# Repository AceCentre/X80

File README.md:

# X80

X80 is an Arduino-based multi-functional input/output device designed to be an interface between assistive technology inputs such as accessibility switches or specilist sensors and mainstream technology outputs, such as to a mobile phone or Augmentative and Alternative Communication (AAC) device.

An X80 can be preprogrammed and repurposed to perform a different function. It's built around the Adafruit Feather, generally the nrf82540 Express. It's essentially a Feather Wing for Assistive Technology (AT).

There are a couple of smilar projects:

https://github.com/google/mimosa

https://github.com/asterics/FABI

The PCB is still a work in progress but it is designed to have:

* Switch inputs via 3.5mm jack
* switch outputs via 3.5mm jack (simulates a switch press as an input into an Assistive Technology device)
* DB9 connector designed to accomodate devices meeting the TRACE SET Standard often used with accessibility input devices (https://park.org/Guests/Trace/pavilion/setdoc1.htm)
* buzzer
* potentiometer
* on/off switch

There are a few differences between the prototype versions:

## Version 4

The funtionality has been split into two boards:

* X80 Standard (designed for Adafruit ItsyBitsy nrf52840 https://www.adafruit.com/product/4481)
* X80 Power (required for LIPO battery as this board includes the chargin circuit)

### X80 Standard

* Majority surface mount components
* 4 switch inputs (5 with splitter cable on one port)
* 4 switch outputs
* One switch 'pass through' (one switch input will still control on switch output without power)
* buzzer
* setting potentiometer
* header for connecting X80 Power or wiring direct to board)

### X80 Power

* JST connector for LIPO battery
* DB9 connector for connecting external peripherals
* will allow space in enclosure for LIPO battery

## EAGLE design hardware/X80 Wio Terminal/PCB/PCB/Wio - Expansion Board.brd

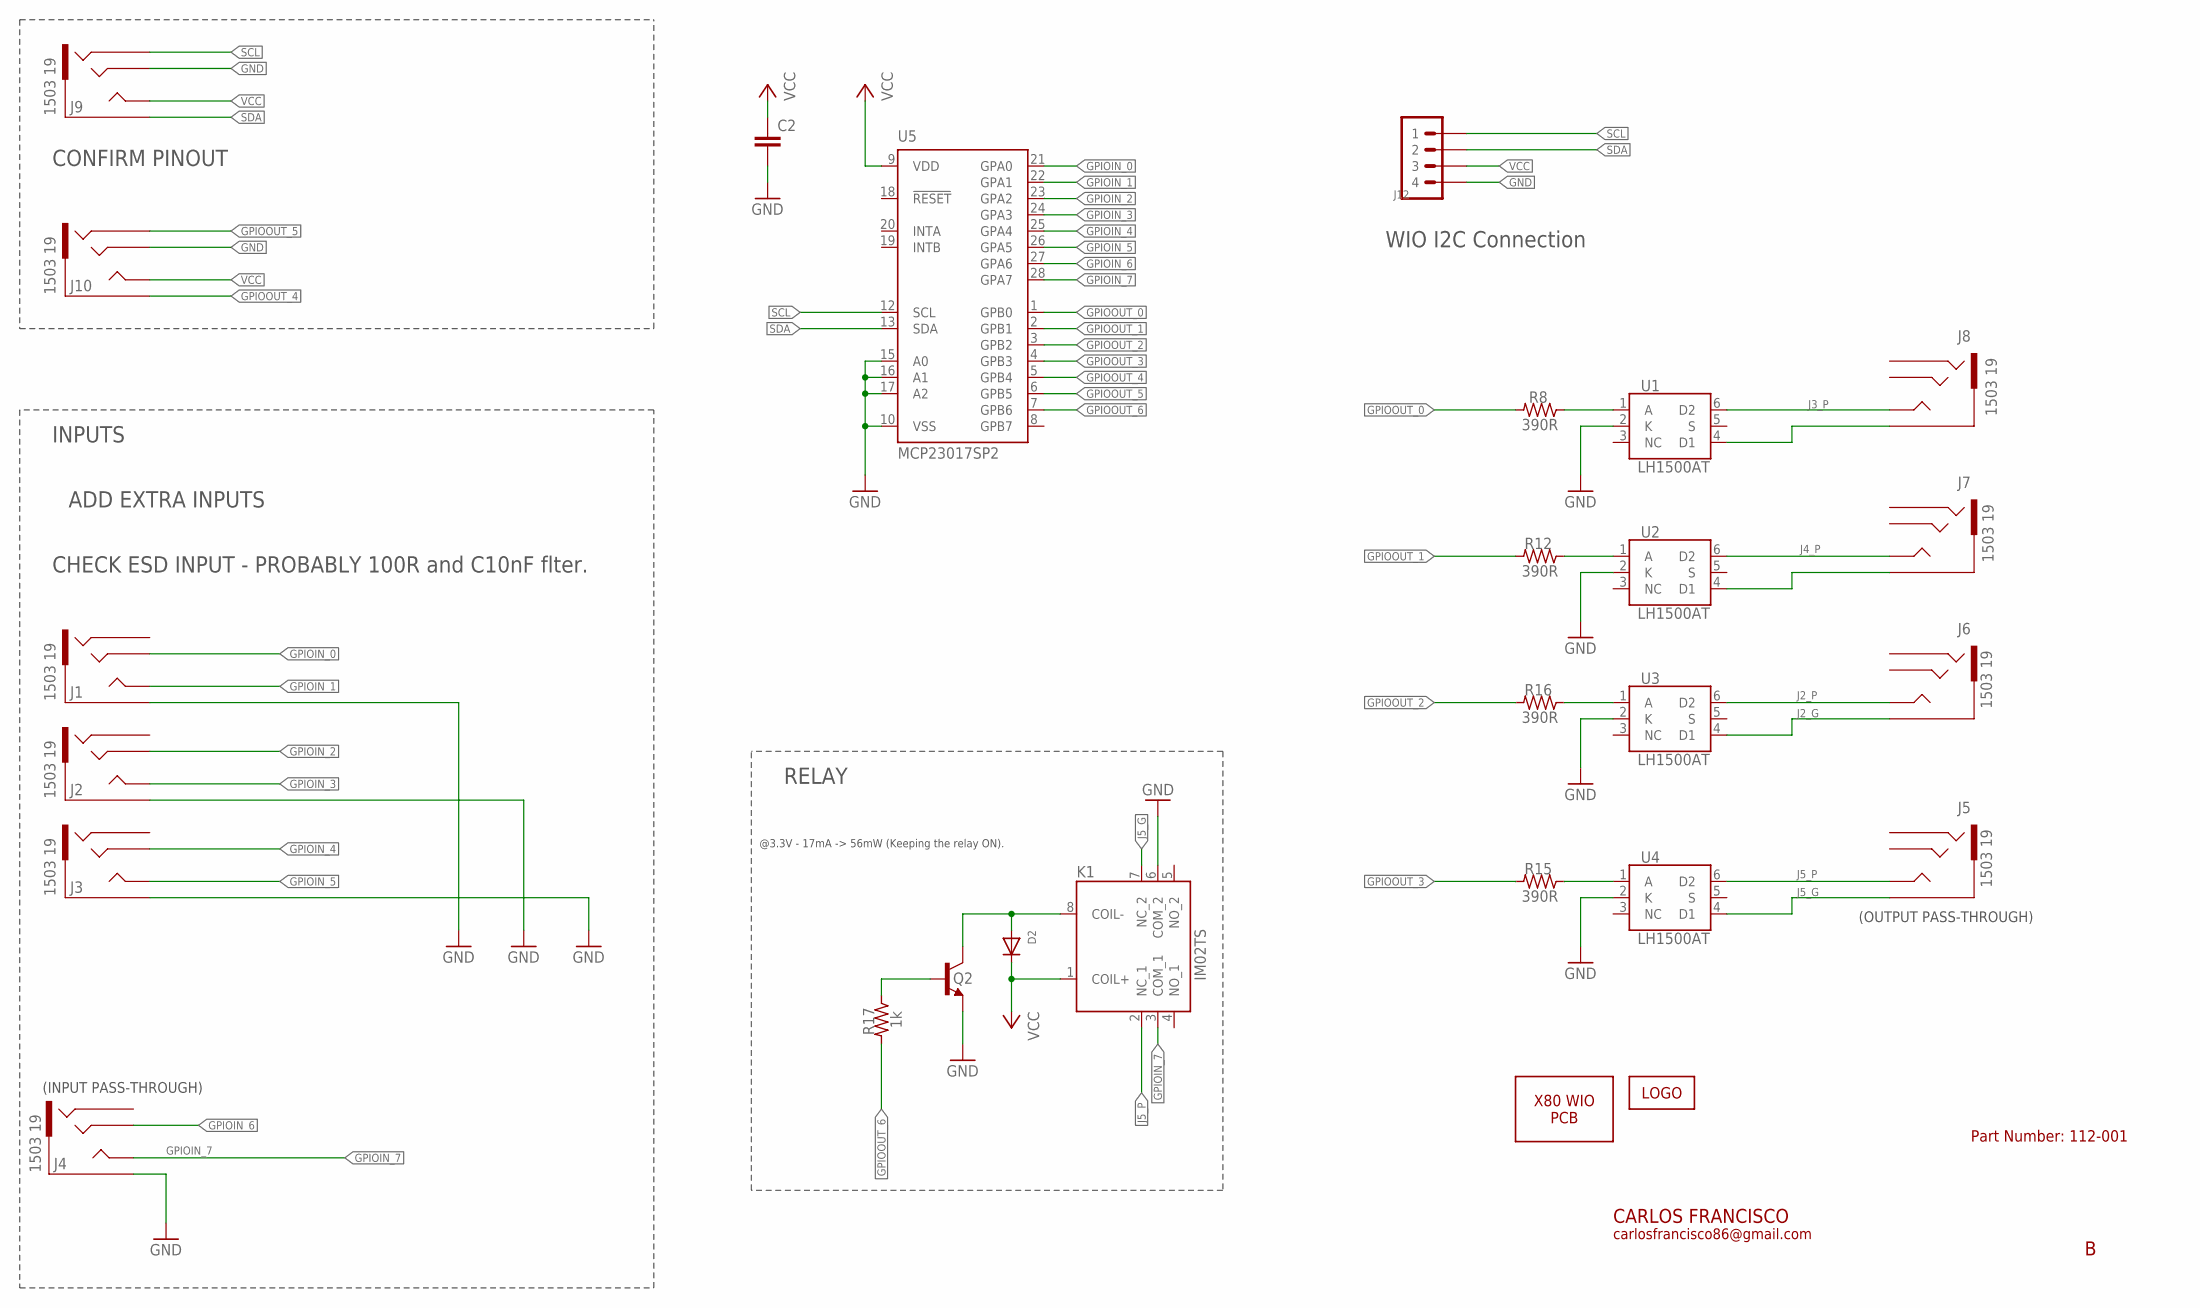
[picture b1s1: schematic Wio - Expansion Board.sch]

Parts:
C2: C-EU025-025X050; C025-025X050
D2: 1N4148; DO-1N4148
J1, J2, J3, J4, J5, J6, J7, J8, J9, J10: 1503 19; 1503-19
J12: 4P-2.0-90D; HW4-2.0-90D
K1: IM02TS; IM03TS114620378
LOGO1: LOGO-10MM; LOGO_10MM
PCB2: X80_WIO_PCB-WIO_PCB_V1; WIO_PCB
Q2: PN2222A; TO92-EBC-OVAL
R8, R12, R15, R16: 390R; 0204/7
R17: 1k; 0204/7
U1, U2, U3, U4: LH1500AT; DIP762W47P254L880H410Q6N
U5: MCP23017SP2; DIL28-3-ROUND

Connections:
GND: C2.2, J1.1, J2.1, J3.1, J4.1, J9.3, J10.3, J12.4, K1.6 (COM_2), Q2.E, U1.2 (K), U2.2 (K), U3.2 (K), U4.2 (K), U5.10 (VSS), U5.15 (A0), U5.16 (A1), U5.17 (A2)
GPIOIN_0: J1.3, U5.21 (GPA0)
GPIOIN_1: J1.4, J1.5 (4), U5.22 (GPA1)
GPIOIN_2: J2.3, U5.23 (GPA2)
GPIOIN_3: J2.4, J2.5 (4), U5.24 (GPA3)
GPIOIN_4: J3.3, U5.25 (GPA4)
GPIOIN_5: J3.4, J3.5 (4), U5.26 (GPA5)
GPIOIN_6: J4.3, U5.27 (GPA6)
GPIOIN_7: J4.4, J4.5 (4), K1.3 (COM_1), U5.28 (GPA7)
GPIOOUT_0: R8.1, U5.1 (GPB0)
GPIOOUT_1: R12.1, U5.2 (GPB1)
GPIOOUT_2: R16.1, U5.3 (GPB2)
GPIOOUT_3: R15.1, U5.4 (GPB3)
GPIOOUT_4: J10.1, U5.5 (GPB4)
GPIOOUT_5: J10.2, U5.6 (GPB5)
GPIOOUT_6: R17.1, U5.7 (GPB6)
J2_G: J6.1, U3.4 (D1)
J2_P: J6.4, J6.5 (4), U3.6 (D2)
J3_P: J8.4, J8.5 (4), U1.6 (D2)
J4_P: J7.4, J7.5 (4), U2.6 (D2)
J5_G: J5.1, K1.7 (NC_2), U4.4 (D1)
J5_P: J5.4, J5.5 (4), K1.2 (NC_1), U4.6 (D2)
unnamed: J8.1, U1.4 (D1)
unnamed: J7.1, U2.4 (D1)
unnamed: R8.2, U1.1 (A)
unnamed: R12.2, U2.1 (A)
unnamed: R16.2, U3.1 (A)
unnamed: R15.2, U4.1 (A)
unnamed: D2.A, K1.8 (COIL-), Q2.C
unnamed: Q2.B, R17.2
SCL: J9.2, J12.1, U5.12 (SCL)
SDA: J9.1, J12.2, U5.13 (SDA)
VCC: C2.1, D2.C, J9.4, J9.5 (4), J10.4, J10.5 (4), J12.3, K1.1 (COIL+), U5.9 (VDD)

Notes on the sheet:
CARLOS FRANCISCO
carlosfrancisco86@gmail.com
(INPUT PASS-THROUGH)
INPUTS
(OUTPUT PASS-THROUGH)
RELAY
Part Number: 112-001
@3.3V - 17mA -> 56mW (Keeping the relay ON).
CONFIRM PINOUT
ADD EXTRA INPUTS
WIO I2C Connection
CHECK ESD INPUT - PROBABLY 100R and C10nF flter.

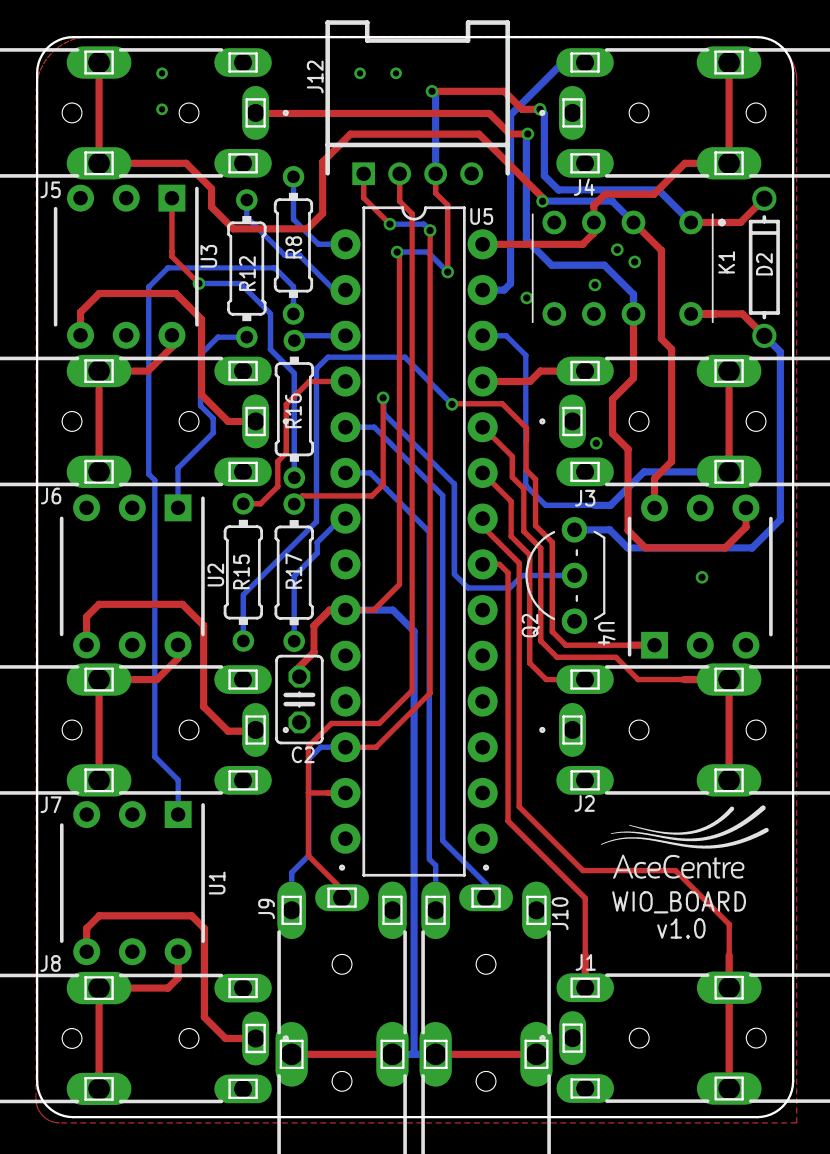
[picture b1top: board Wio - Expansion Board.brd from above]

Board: 2 copper layers, 42.0 x 60.0 mm, 27 parts (0 on the bottom side), 33 nets.

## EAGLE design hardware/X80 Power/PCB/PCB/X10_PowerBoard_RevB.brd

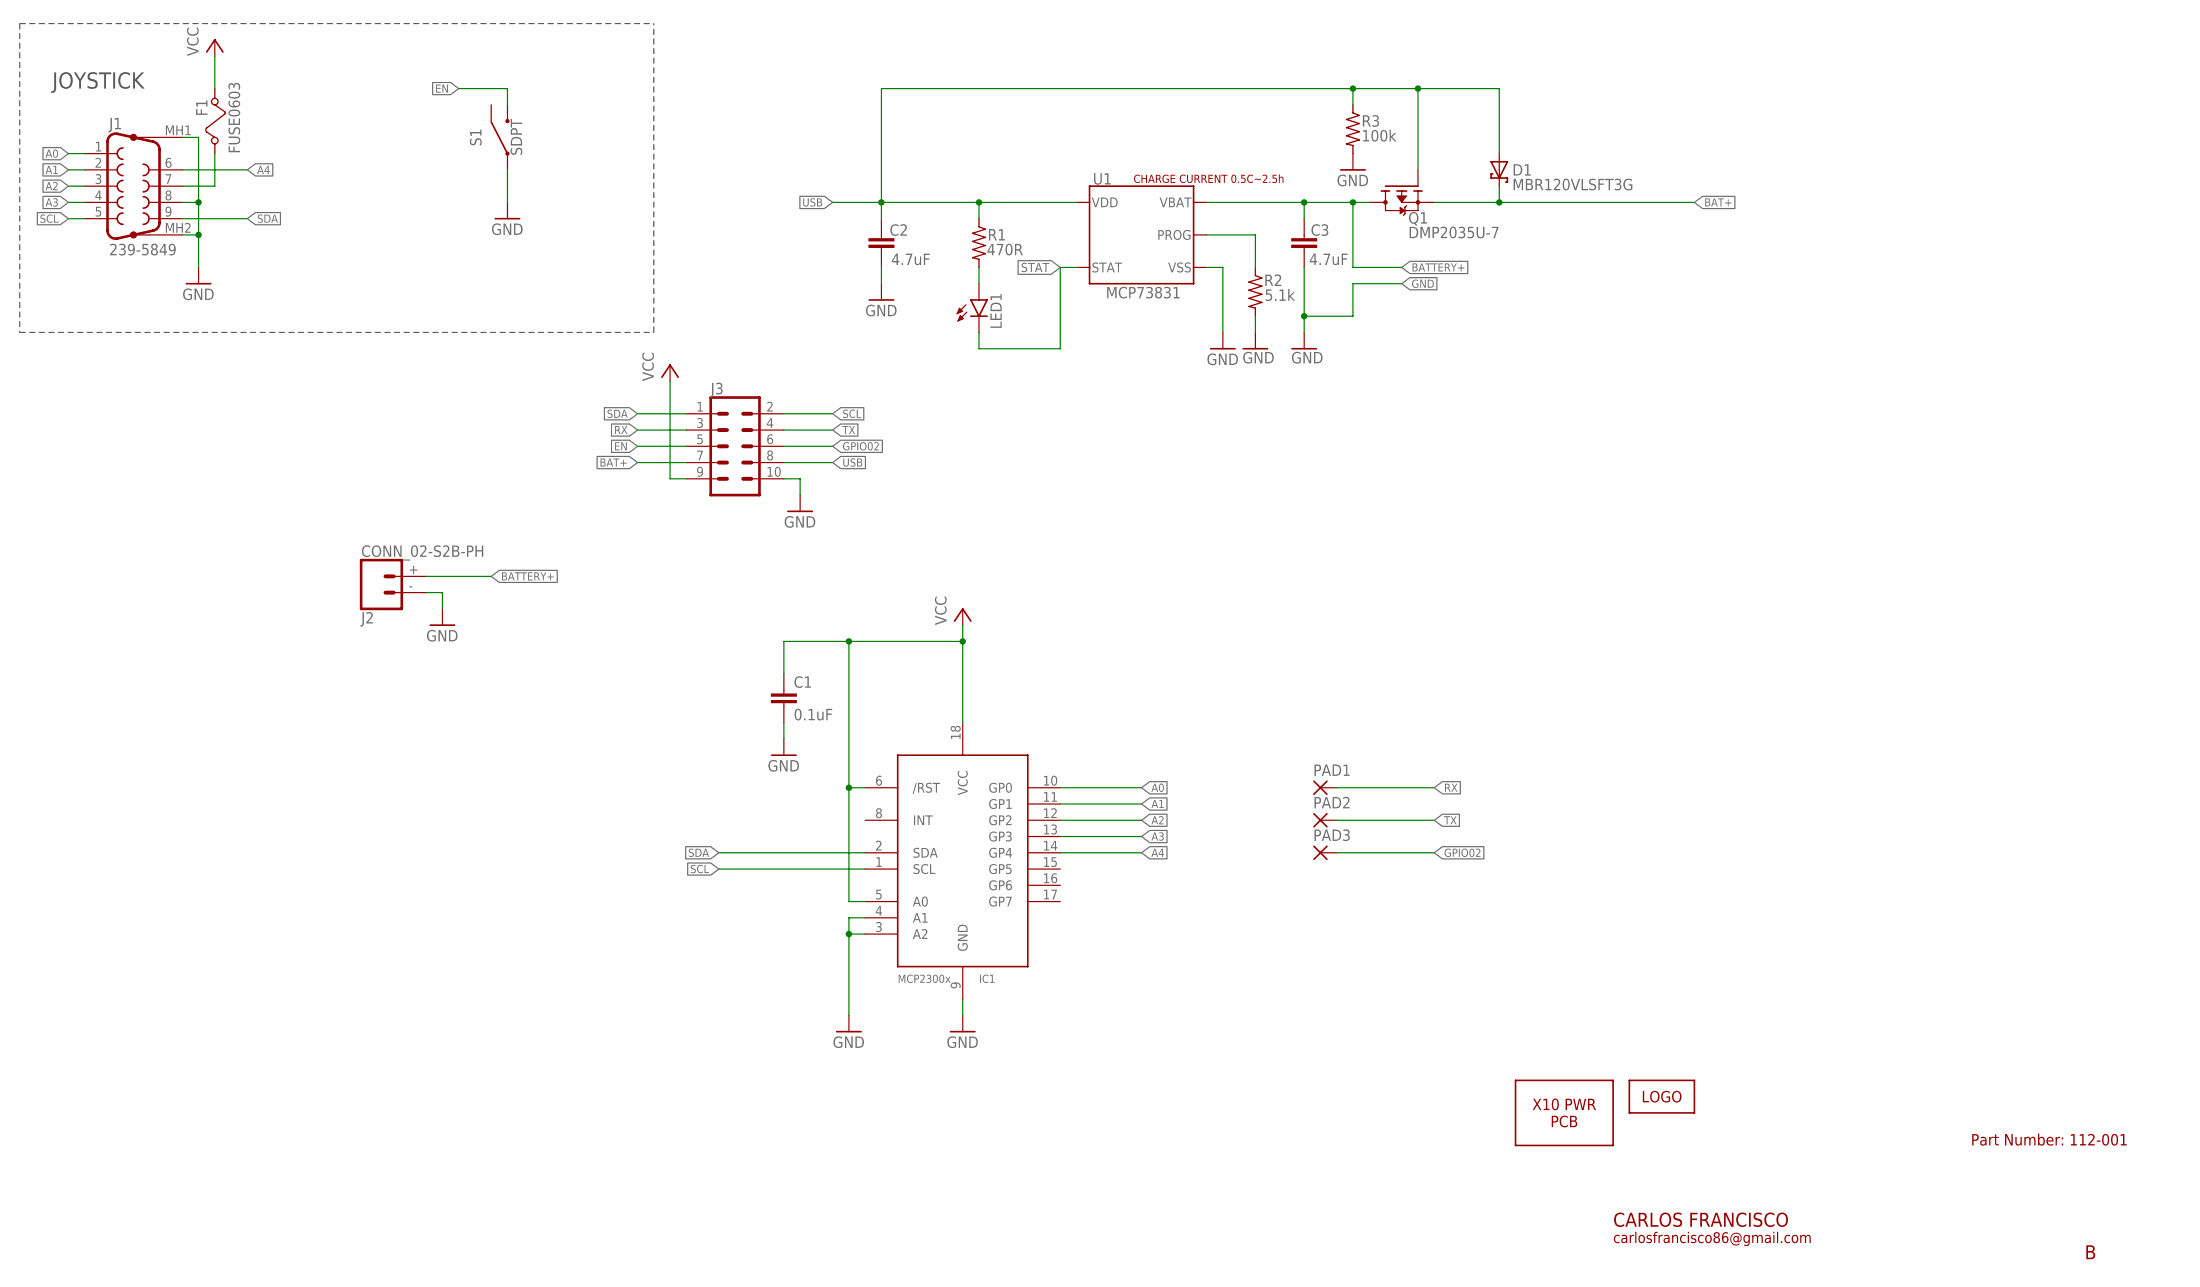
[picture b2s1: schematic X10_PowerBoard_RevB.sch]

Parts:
C1: 0.1uF; C0603
C2, C3: 4.7uF; CAPC1608X85
D1: MBR120VLSFT3G; SODFL3616X98N
F1: FUSE0603; FUSC1607X75N
IC1: MCP23008/P; DIL18
J1: 239-5849; DB9_PLUG_SLOT
J2: CONN_02-S2B-PH; S2B-PH-RA
J3: CONN2_05-HEADER; 2X5_HEADER
LED1: LEDSML0603; SML0603
LOGO1: LOGO-10MM; LOGO_10MM
PAD1, PAD2, PAD3: 1,6/0,8
PCB1: X10_PWR_PCB-X10_PWR_PCB; X10_POWER_PCB
Q1: DMP2035U-7; SOT95P230X110-3N
R1: 470R; RESC1608X60
R2: 5.1k; RESC1608X60
R3: 100k; RESC1608X60
S1: SDPT; OS102011MA1QN1
U1: MCP73831; SOT23-5P95_270X145L35X35N

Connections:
A0: IC1.10 (GP0), J1.1
A1: IC1.11 (GP1), J1.2
A2: IC1.12 (GP2), J1.3
A3: IC1.13 (GP3), J1.4
A4: IC1.14 (GP4), J1.6
BAT+: D1.K (C), J3.7, Q1.2 (S)
BATTERY+: C3.1, J2.+ (1), Q1.3 (D), U1.3 (VBAT)
EN: J3.5, S1.1
GND: C1.2, C2.2, C3.2, IC1.3 (A2), IC1.4 (A1), IC1.9 (GND), J1.8, J1.MH1 (G1), J1.MH2 (G2), J2.- (2), J3.10, R2.1, R3.1, S1.2, U1.2 (VSS)
GPIO02: J3.6, PAD3.1
unnamed: LED1.A, R1.1
unnamed: F1.1, J1.7
unnamed: R2.2, U1.5 (PROG)
RX: J3.3, PAD1.1
SCL: IC1.1 (SCL), J1.5, J3.2
SDA: IC1.2 (SDA), J1.9, J3.1
STAT: LED1.C, U1.1 (STAT)
TX: J3.4, PAD2.1
USB: C2.1, D1.A, J3.8, Q1.1 (G), R1.2, R3.2, U1.4 (VDD)
VCC: C1.1, F1.2, IC1.5 (A0), IC1.6 (/RST), IC1.18 (VCC), J3.9

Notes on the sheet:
CARLOS FRANCISCO
carlosfrancisco86@gmail.com
JOYSTICK
Part Number: 112-001
CHARGE CURRENT 0.5C~2.5h

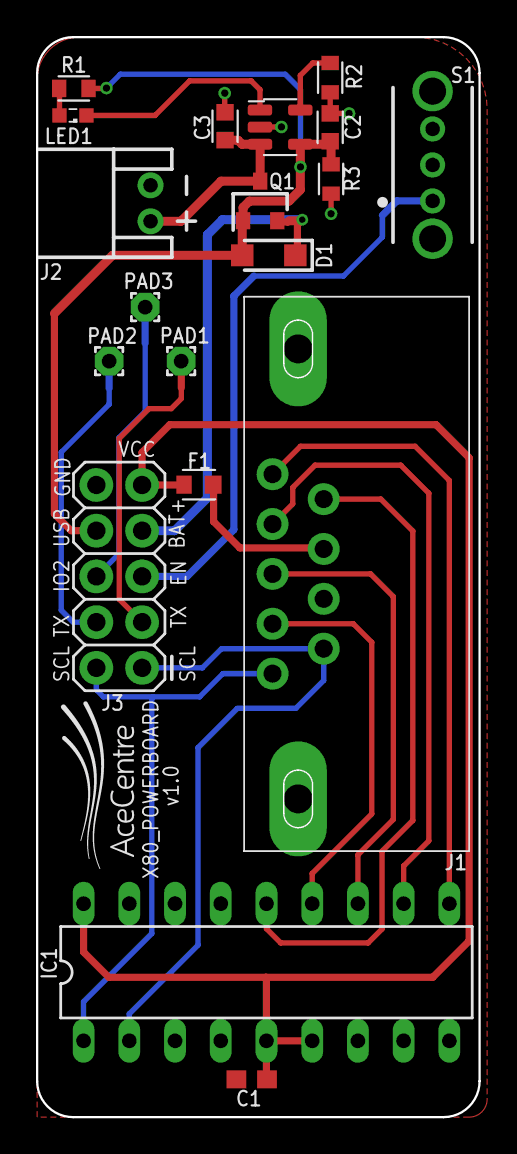
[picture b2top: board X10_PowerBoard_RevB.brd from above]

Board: 2 copper layers, 24.6 x 60.0 mm, 21 parts (0 on the bottom side), 20 nets.

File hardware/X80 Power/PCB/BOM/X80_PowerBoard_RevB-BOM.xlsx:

Item # | Ref Des | Qty | Description | Manufacturer | Manufacturer part-name | Value | Package
1 | C1 | 1 | CAP CER 0.1UF 25V X7R 0603 | KEMET | C0603C104K3RAC7411 | 0.1uF | 0603
2 | C2, C3 | 2 | CAP CER 4.7UF 10V X5R 0603 | Samsung Electro-Mechanics | CL10A475KP8NNNC | 4.7uF | 0603
3 | D1 | 1 | Semiconductor DIODE SCHOTTKY 20V 1A SOD123FL | On Semiconductor | MBR120VLSFT3G | MBR120VLSFT3G | SOD-123FL
4 | F1 | 1 | PTC RESET FUSE 6V 500MA 0603 | Bourns | MF-FSMF050X-2 | FUSE0603 | 0603
5 | IC1 | 1 | IC I/O EXPANDER I2C 8B 18DIP | Microchip Technology | MCP23008-E/P | MCP23008/P | DIP-18
6 | J1 | 1 | D-sub Connector - 2.77mm Pitch | RS Pro | 239-5849 | 239-5849 | THT
7 | J2 | 1 | CONN HEADER R/A 2POS 2MM | JST Sales America Inc. | S2B-PH-K-S(LF)(SN) | CONN_02-S2B-PH | THT
10 | J3 | 1 | CONN HEADER VERT 10POS 2.54MM | Adam Tech | PH2-10-UA | CONN2_05-HEADER | THT
11 | LED1 | 1 | LED RED DIFFUSED 0603 SMD | Würth Elektronik | 150060SS55040 | RED | 0603
12 | Q1 | 1 | MOSFET P-CH 20V 3.6A SOT-23 | Diodes Incorporated | DMP2035U-7 | DMP2035U-7 | 0603
13 | R1 | 1 | RES SMD 470 OHM 1% 1/10W 0603 | Yageo | RC0603FR-07470RL | 470R | 0603
14 | R2 | 1 | RES SMD 5.1K OHM 1% 1/10W 0603 | Yageo | RC0603FR-075K1L | 5.1k | 0603
15 | R3 | 1 | RES SMD 100K OHM 1% 1/10W 0603 | Yageo | RC0603FR-07100KL | 100k | THT
16 | S1 | 1 | Switch Slide Right Angle SPDT 0.1A 12VDC Through Hole Slide Switch SPDT On-On 0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 | C & K COMPONENTS | OS102011MA1QN1 | SDPT | 0603
17 | U1 | 1 | Single-Cell, Fully Integrated Li-Ion,Li-Polymer Charge Management Controllers | Microchip | MCP73831T-2ACI/OT | MCP73831 | 0603

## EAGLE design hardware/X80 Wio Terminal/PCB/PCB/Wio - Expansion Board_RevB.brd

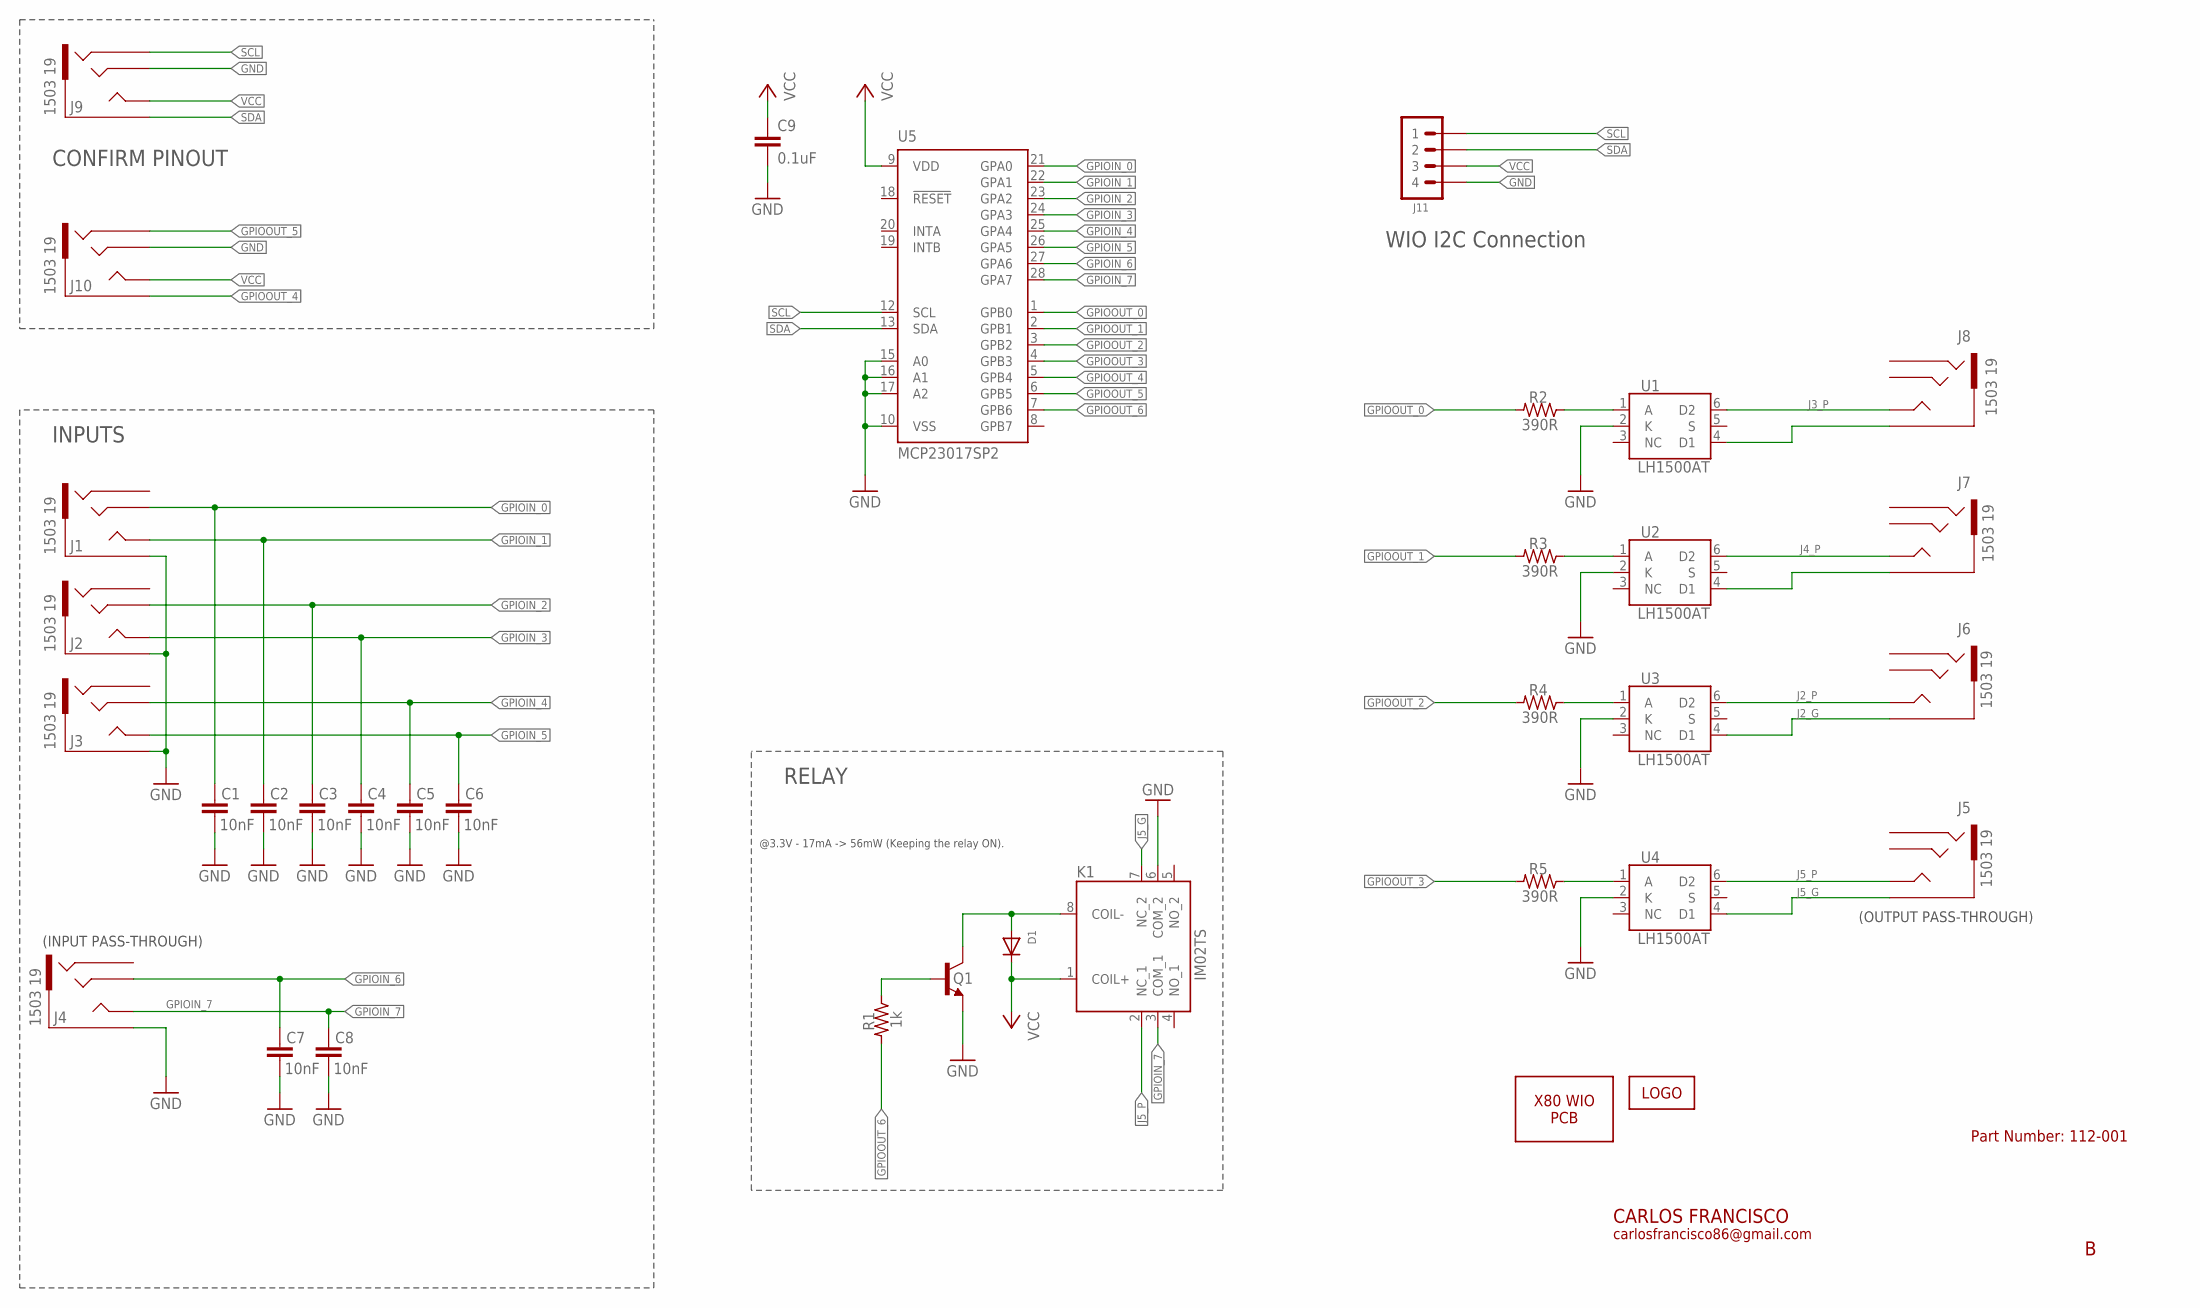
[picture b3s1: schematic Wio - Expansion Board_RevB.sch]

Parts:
C1, C2, C3, C4, C5, C6, C7, C8: 10nF; C025-024X044
C9: 0.1uF; C025-025X050
D1: 1N4148; DO-1N4148
J1, J2, J3, J4, J5, J6, J7, J8, J9, J10: 1503 19; 1503-19
J11: 4P-2.0-90D; HW4-2.0-90D
K1: IM02TS; IM03TS114620378
LOGO1: LOGO-10MM; LOGO_10MM
PCB2: X80_WIO_PCB-WIO_PCB_V1; WIO_PCB
Q1: PN2222A; TO92-EBC-OVAL
R1: 1k; 0204/7
R2, R3, R4, R5: 390R; 0204/7
U1, U2, U3, U4: LH1500AT; DIP762W47P254L880H410Q6N
U5: MCP23017SP2; DIL28-3-ROUND

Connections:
GND: C1.2, C2.2, C3.2, C4.2, C5.2, C6.2, C7.2, C8.2, C9.2, J1.1, J2.1, J3.1, J4.1, J9.3, J10.3, J11.4, K1.6 (COM_2), Q1.E, U1.2 (K), U2.2 (K), U3.2 (K), U4.2 (K), U5.10 (VSS), U5.15 (A0), U5.16 (A1), U5.17 (A2)
GPIOIN_0: C1.1, J1.3, U5.21 (GPA0)
GPIOIN_1: C2.1, J1.4, J1.5 (4), U5.22 (GPA1)
GPIOIN_2: C3.1, J2.3, U5.23 (GPA2)
GPIOIN_3: C4.1, J2.4, J2.5 (4), U5.24 (GPA3)
GPIOIN_4: C5.1, J3.3, U5.25 (GPA4)
GPIOIN_5: C6.1, J3.4, J3.5 (4), U5.26 (GPA5)
GPIOIN_6: C7.1, J4.3, U5.27 (GPA6)
GPIOIN_7: C8.1, J4.4, J4.5 (4), K1.3 (COM_1), U5.28 (GPA7)
GPIOOUT_0: R2.1, U5.1 (GPB0)
GPIOOUT_1: R3.1, U5.2 (GPB1)
GPIOOUT_2: R4.1, U5.3 (GPB2)
GPIOOUT_3: R5.1, U5.4 (GPB3)
GPIOOUT_4: J10.1, U5.5 (GPB4)
GPIOOUT_5: J10.2, U5.6 (GPB5)
GPIOOUT_6: R1.1, U5.7 (GPB6)
J2_G: J6.1, U3.4 (D1)
J2_P: J6.4, J6.5 (4), U3.6 (D2)
J3_P: J8.4, J8.5 (4), U1.6 (D2)
J4_P: J7.4, J7.5 (4), U2.6 (D2)
J5_G: J5.1, K1.7 (NC_2), U4.4 (D1)
J5_P: J5.4, J5.5 (4), K1.2 (NC_1), U4.6 (D2)
unnamed: J8.1, U1.4 (D1)
unnamed: J7.1, U2.4 (D1)
unnamed: R2.2, U1.1 (A)
unnamed: R3.2, U2.1 (A)
unnamed: R4.2, U3.1 (A)
unnamed: R5.2, U4.1 (A)
unnamed: D1.A, K1.8 (COIL-), Q1.C
unnamed: Q1.B, R1.2
SCL: J9.2, J11.1, U5.12 (SCL)
SDA: J9.1, J11.2, U5.13 (SDA)
VCC: C9.1, D1.C, J9.4, J9.5 (4), J10.4, J10.5 (4), J11.3, K1.1 (COIL+), U5.9 (VDD)

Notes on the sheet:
CARLOS FRANCISCO
carlosfrancisco86@gmail.com
(INPUT PASS-THROUGH)
INPUTS
(OUTPUT PASS-THROUGH)
RELAY
Part Number: 112-001
@3.3V - 17mA -> 56mW (Keeping the relay ON).
CONFIRM PINOUT
WIO I2C Connection

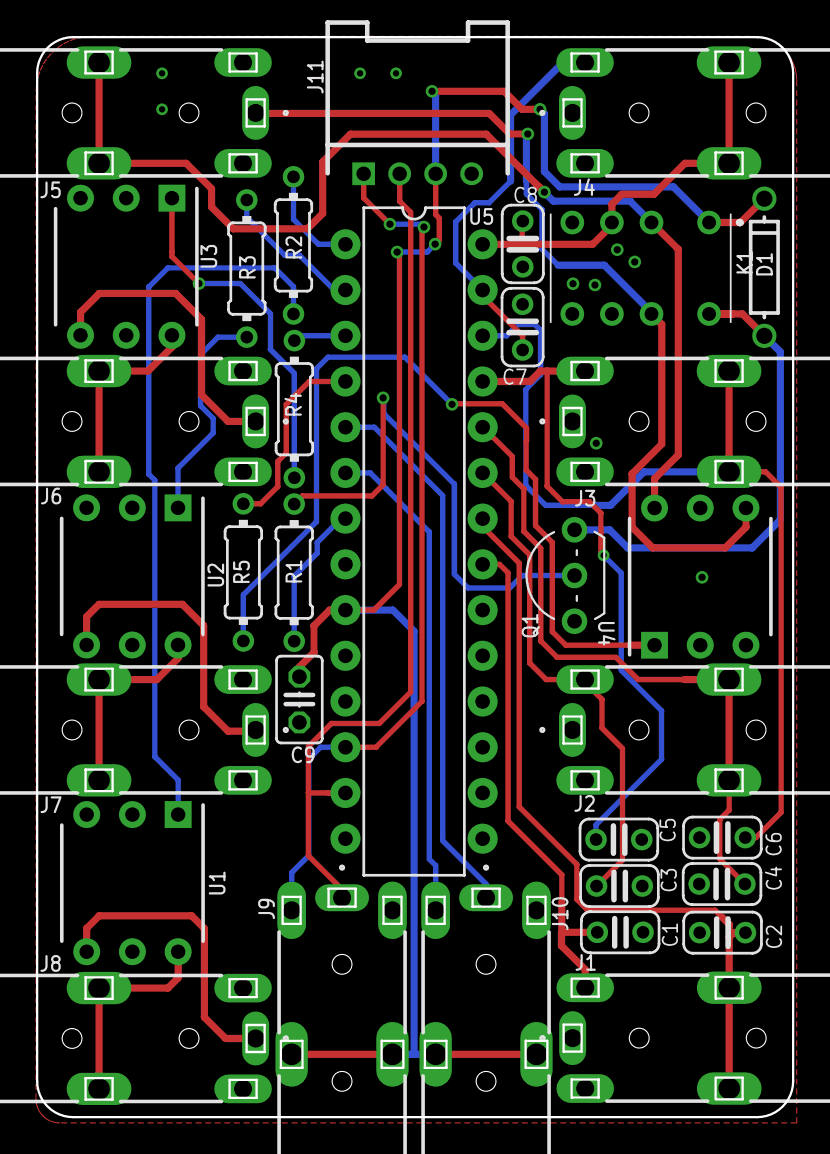
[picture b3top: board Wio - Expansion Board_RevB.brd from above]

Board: 2 copper layers, 42.0 x 60.0 mm, 35 parts (1 on the bottom side), 33 nets.

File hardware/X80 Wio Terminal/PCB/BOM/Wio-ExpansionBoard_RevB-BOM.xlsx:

Item # | Ref Des | Qty | Description | Manufacturer | Manufacturer part-name | Value | Package | RS-ONLINE_NUM
1 | C1, C2, C3, C4, C5, C6, C7, C8 | 8 | 10nF Multilayer Ceramic Capacitor MLCC 50V dc ±10% | KEMET | C315C103K5R5TA | 10nF | THT | 538-1196
2 | C9 | 1 | Murata 100nF Multilayer Ceramic Capacitor MLCC 50V dc ±15% | Murata | RCER71H104K0K1H03B | 100nF | THT | 841-0749
3 | D1 | 1 | Switching Diode, 400mA 100V, 2-Pin DO-35 1N4148TR | On Semiconductor | 1N4148TR | 1N4148 | THT | 671-5477
4 | J1, J2, J3, J4, J5, J6, J7, J8, J9, J10 | 10 | 3.5 mm PCB Mount Stereo Jack Socket, 4Pole 1A | Lumberg | 1503 19 | Stereo Jack | THT | 124-8885
5 | J11 | 1 | Groove Female Header - DIP-4P-2,0mm-90D |  |  |  | THT | https://www.seeedstudio.com/Grove-Universal-4-pin-connector-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
6 | K1 | 1 | DPDT telecom PCB relay, 2A 3Vdc coil, EA | TE Connectivity | 1462037-4 | IM01TS | THT | 909-7996
7 | Q1 | 1 | NPN General-Purpose Amplifier | On Semiconductor | PN2222ABU | PN2222A | TO-92 | 739-0555
8 | R1 | 1 | RS PRO 1kΩ Carbon Film Resistor 0.25W ±5% | RS PRO | 707-7666 | 1k | THT | 707-7666
9 | R2, R3, R4, R5 | 4 | RS PRO 390Ω Carbon Film Resistor 0.25W ±5% | RS PRO | 707-7634 | 390R | THT | 707-7634
10 | U1, U2, U3, U4 | 4 | 1 Form A Solid-State Relay (NO) | Vishay | LH1500AT | LH1500AT | PDIP-6 | 180-8794
11 | U5 | 1 | IC I/O EXPANDER I2C 16-Bit 28SDIP | Microchip | MCP23017-E/SP | MCP23017 | PDIP28 | 144-5723

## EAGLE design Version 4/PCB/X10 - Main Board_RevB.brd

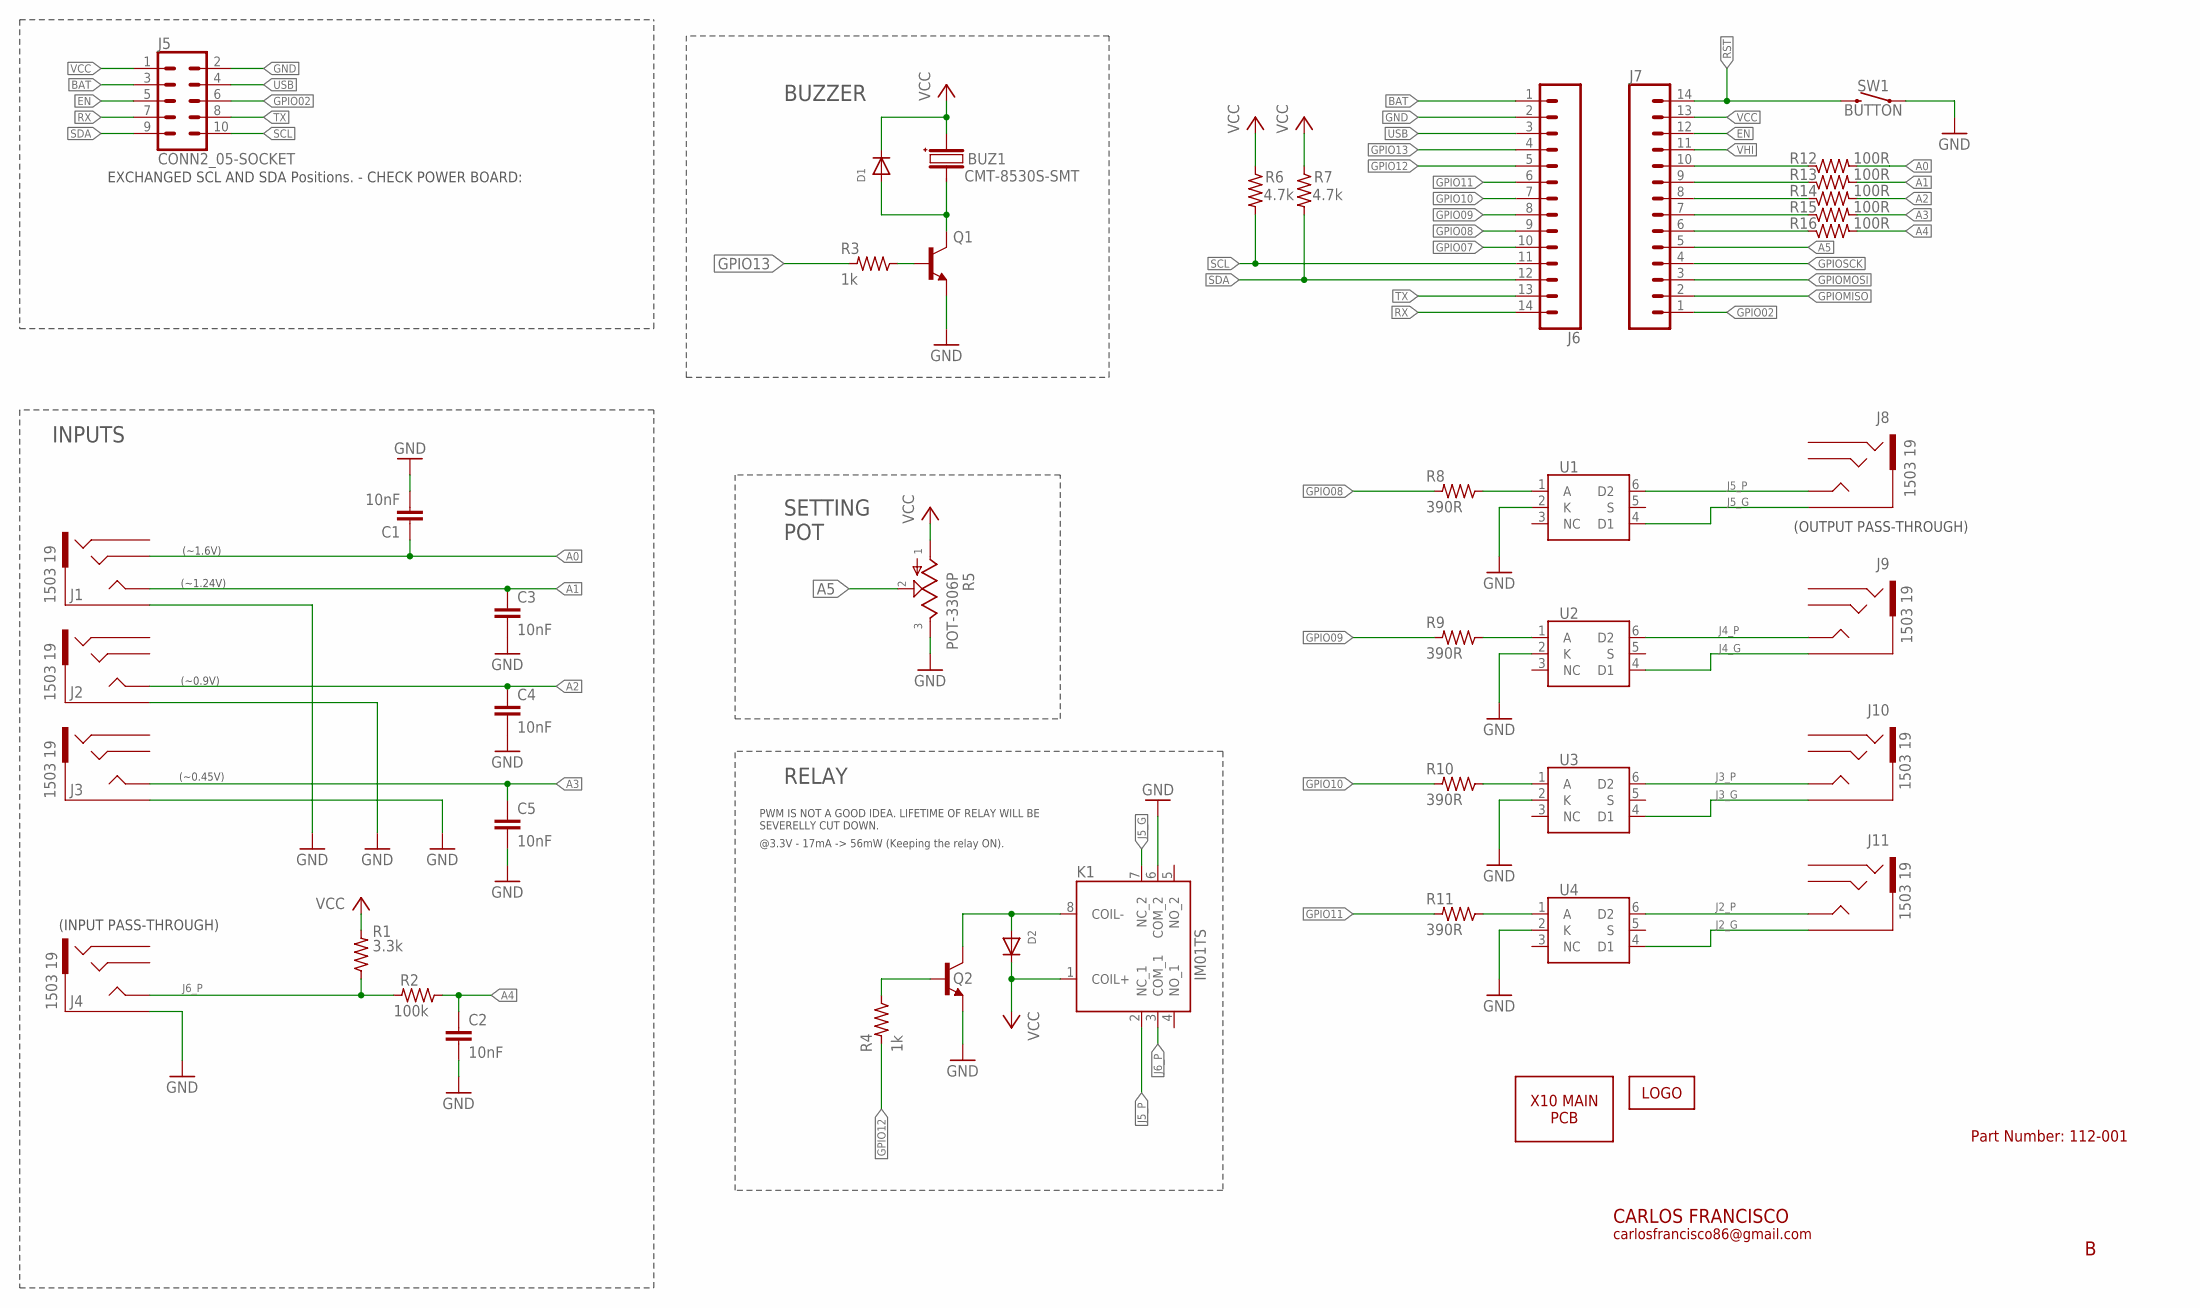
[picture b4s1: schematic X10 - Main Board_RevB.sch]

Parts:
BUZ1: CMT-8530S-SMT; CMT8530SSMTTR
C1, C2, C3, C4, C5: 10nF; CAPC1608X85
D1, D2: DIODE-SOD-123; SOD-123
J1, J2, J3, J4, J8, J9, J10, J11: 1503 19; 1503-19
J5: CONN2_05-SOCKET; 2X5_SOCKET
J6, J7: CONN_14; 1X14
K1: IM01TS; IM03TS114620378
LOGO1: LOGO-10MM; LOGO_10MM
PCB1: X10_MAIN_PCB-X10_MAIN; X10_MAIN_PCB
Q1, Q2: NPN-SOT-23; SOT-23
R1: 3.3k; R0603
R2: 100k; R0603
R3, R4: 1k; R0603
R5: POT-3306P; 3306P1103
R6, R7: 4.7k; R0603
R8, R9, R10, R11: 390R; R0603
R12, R13, R14, R15, R16: 100R; R0603
SW1: BUTTON; SERIES95C_RA
U1, U2, U3, U4: LH1500AT; DIP762W47P254L880H410Q6N

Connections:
A0: C1.1, J1.3, R12.1
A1: C3.1, J1.4, J1.5 (4), R13.1
A2: C4.1, J2.4, J2.5 (4), R14.1
A3: C5.1, J3.4, J3.5 (4), R15.1
A4: C2.1, R2.2, R16.1
A4_R: J7.6, R16.2
A5: J7.5, R5.2
BAT: J5.3, J6.1
BUZ_CTRL_R: Q1.B, R3.2
EN: J5.5, J7.12
GND: C1.2, C2.2, C3.2, C4.2, C5.2, J1.1, J2.1, J3.1, J4.1, J5.2, J6.2, K1.6 (COM_2), Q1.E, Q2.E, R5.3, SW1.T1 (1), U1.2 (K), U2.2 (K), U3.2 (K), U4.2 (K)
GPIO02: J5.6, J7.1
GPIO07: J6.10
GPIO08: J6.9, R8.1
GPIO09: J6.8, R9.1
GPIO10: J6.7, R10.1
GPIO11: J6.6, R11.1
GPIO12: J6.5, R4.1
GPIO13: J6.4, R3.1
GPIOMISO: J7.2
GPIOMOSI: J7.3
GPIOSCK: J7.4
J2_G: J11.1, U4.4 (D1)
J2_P: J11.4, J11.5 (4), U4.6 (D2)
J3_G: J10.1, U3.4 (D1)
J3_P: J10.4, J10.5 (4), U3.6 (D2)
J4_G: J9.1, U2.4 (D1)
J4_P: J9.4, J9.5 (4), U2.6 (D2)
J5_G: J8.1, K1.7 (NC_2), U1.4 (D1)
J5_P: J8.4, J8.5 (4), K1.2 (NC_1), U1.6 (D2)
J6_P: J4.4, J4.5 (4), K1.3 (COM_1), R1.2, R2.1
unnamed: BUZ1.3 (-), D1.A, Q1.C
unnamed: J7.10, R12.2
unnamed: J7.9, R13.2
unnamed: J7.8, R14.2
unnamed: J7.7, R15.2
unnamed: R8.2, U1.1 (A)
unnamed: R9.2, U2.1 (A)
unnamed: R11.2, U4.1 (A)
unnamed: R10.2, U3.1 (A)
unnamed: D2.A, K1.8 (COIL-), Q2.C
unnamed: Q2.B, R4.2
RST: J7.14, SW1.T2 (2)
RX: J5.7, J6.14
SCL: J5.10, J6.11, R6.1
SDA: J5.9, J6.12, R7.1
TX: J5.8, J6.13
USB: J5.4, J6.3
VCC: BUZ1.2 (+), D1.C, D2.C, J5.1, J7.13, K1.1 (COIL+), R1.1, R5.1, R6.2, R7.2
VHI: J7.11

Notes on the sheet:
CARLOS FRANCISCO
carlosfrancisco86@gmail.com
BUZZER
SETTING POT
(INPUT PASS-THROUGH)
INPUTS
(OUTPUT PASS-THROUGH)
RELAY
PWM IS NOT A GOOD IDEA. LIFETIME OF RELAY WILL BE SEVERELLY CUT DOWN.
Part Number: 112-001
@3.3V - 17mA -> 56mW (Keeping the relay ON).
(~1.6V)
(~1.24V)
(~0.9V)
(~0.45V)
EXCHANGED SCL AND SDA Positions. - CHECK POWER BOARD:

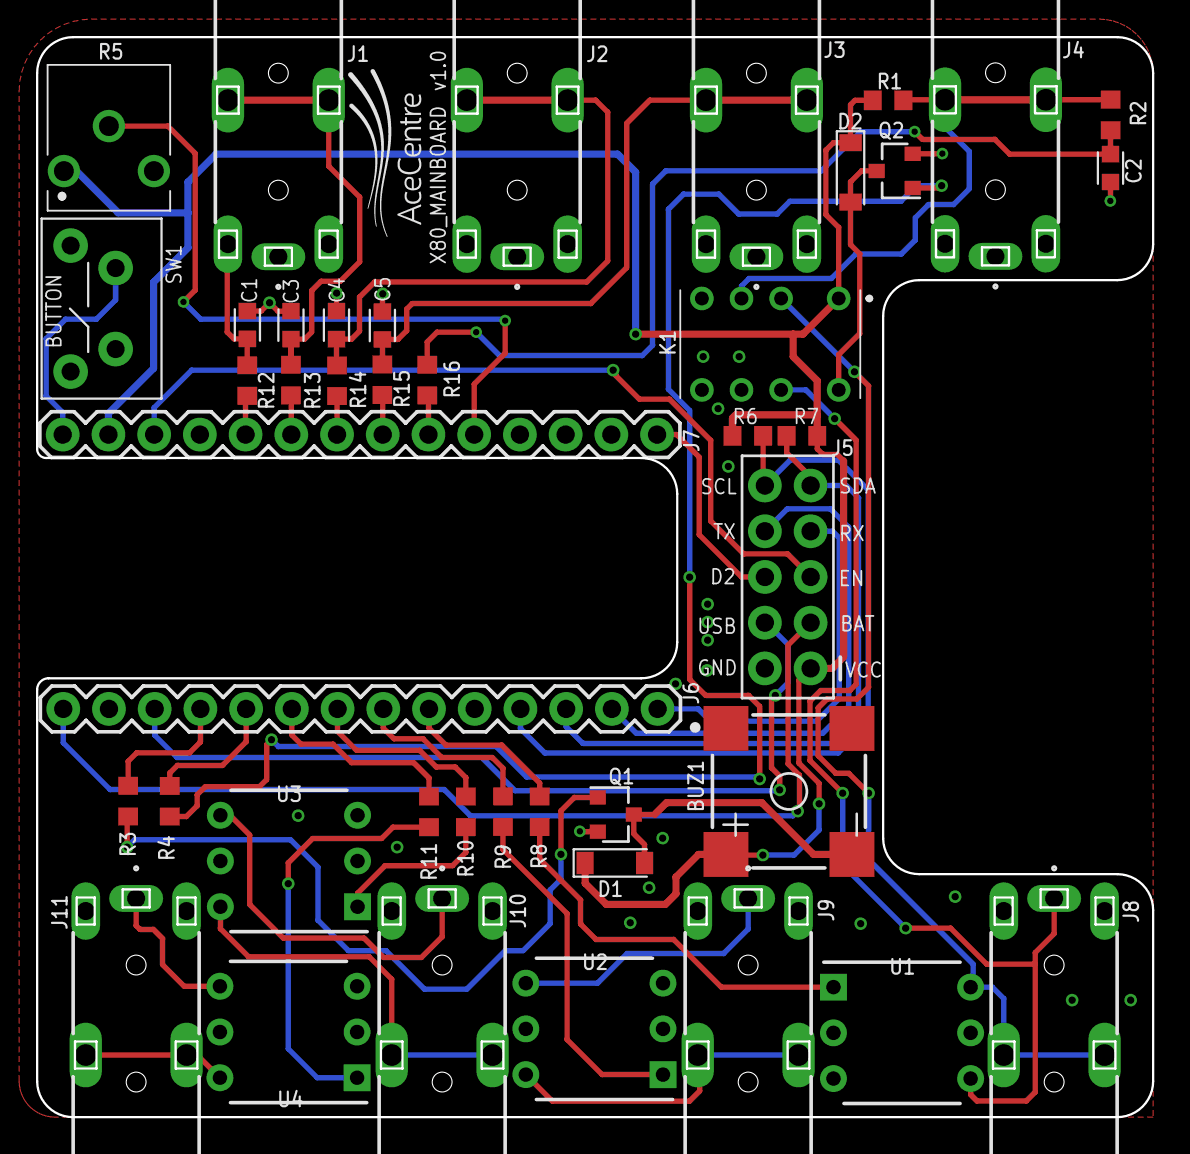
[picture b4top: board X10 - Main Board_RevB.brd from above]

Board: 2 copper layers, 62.0 x 60.0 mm, 45 parts (0 on the bottom side), 45 nets.

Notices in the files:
parts and their libraries:
SparkFun-Connectors: Licensing: Creative Commons ShareAlike 4.0 International - https://creativecommons.org/licenses/by-sa/4.0
